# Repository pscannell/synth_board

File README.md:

# Synth Board

KiCad source files for synth hardware.

## Requirements

Kicad v6 ([download](kicad-unified-6.0.11-0.dmg))

## Getting Started

Open `synth.kicad_pro` from KiCad -> Open Project

Ensure that sch & pcb files can be opened

## Schematics

[See PDFs here](./docs/schematics/synth.pdf)

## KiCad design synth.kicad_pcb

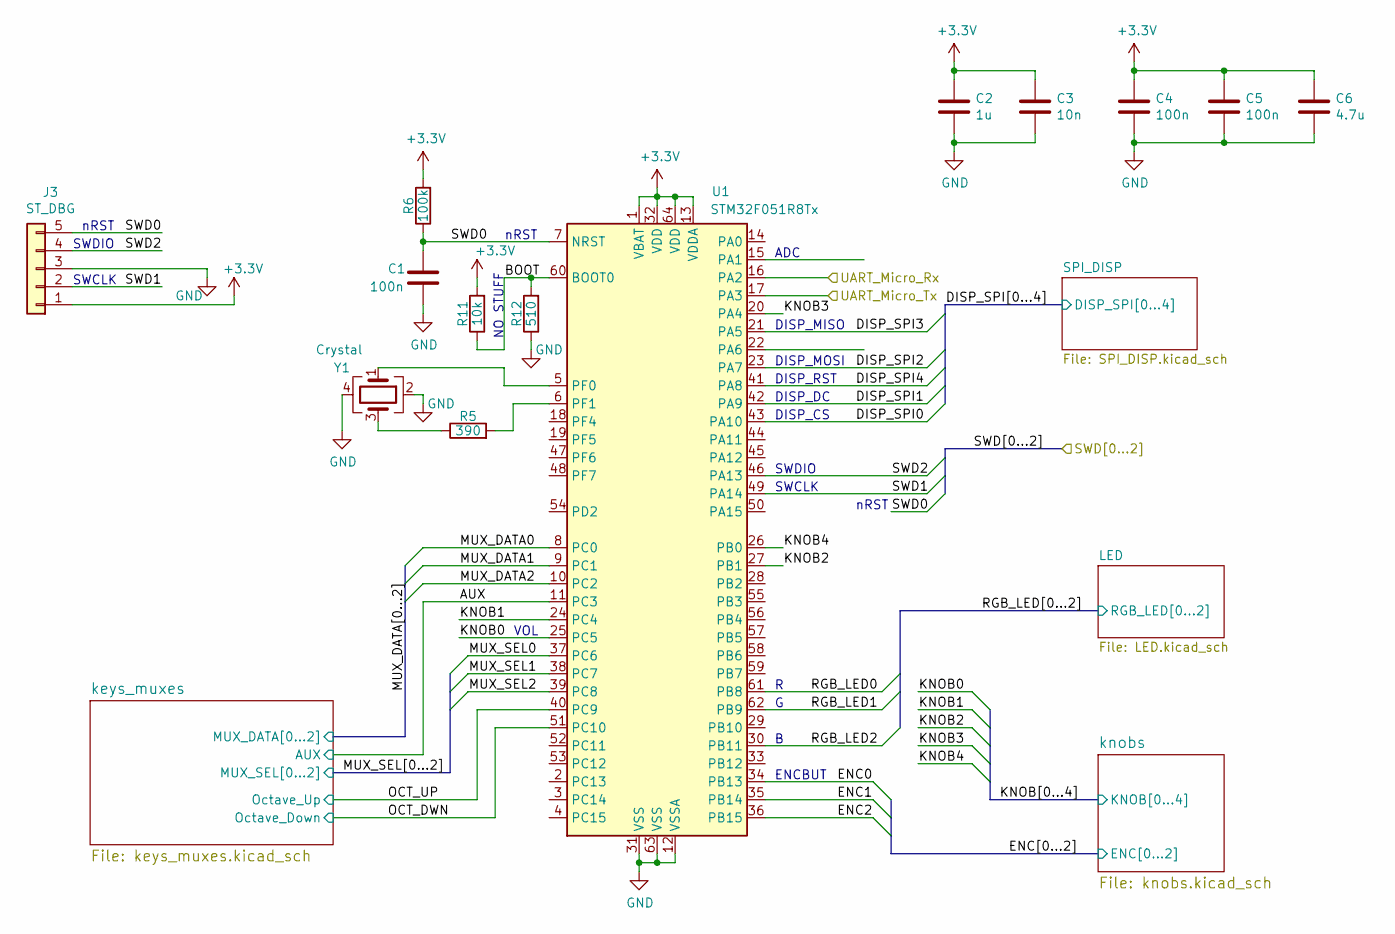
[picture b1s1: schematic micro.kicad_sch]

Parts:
C1, C4, C5: 100n; C_0603_HandSoldering
C2: 1u; C_0603_HandSoldering
C3: 10n; C_0603_HandSoldering
C6: 4.7u; C_0603_HandSoldering
J3: ST_DBG; Pin_Header_Straight_1x05_Pitch2.54mm
R5: 390; R_0603_HandSoldering
R6: 100k; R_0603_HandSoldering
R11: 10k; R_0603_HandSoldering
R12: 510; R_0603_HandSoldering
U1: STM32F051R8Tx; LQFP-64_10x10mm_Pitch0.5mm
Y1: Crystal; Crystal_SMD_Abracon_ABM3B-4pin_5.0x3.2mm

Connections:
/Raspberry_Pi_3/SWD0: C1.1, J3.5, R6.1, U1.7 (NRST); also elsewhere on the board
/Raspberry_Pi_3/SWD1: J3.2, U1.49 (PA14); also elsewhere on the board
/Raspberry_Pi_3/SWD2: J3.4, U1.46 (PA13); also elsewhere on the board
/micro/AUX: U1.11 (PC3); also elsewhere on the board
/micro/BOOT: R11.1, R12.2, U1.60 (BOOT0)
/micro/DISP_SPI0: U1.43 (PA10); also elsewhere on the board
/micro/DISP_SPI1: U1.42 (PA9); also elsewhere on the board
/micro/DISP_SPI2: U1.23 (PA7); also elsewhere on the board
/micro/DISP_SPI3: U1.21 (PA5); also elsewhere on the board
/micro/DISP_SPI4: U1.41 (PA8); also elsewhere on the board
/micro/ENC0: U1.34 (PB13); also elsewhere on the board
/micro/ENC1: U1.35 (PB14); also elsewhere on the board
/micro/ENC2: U1.36 (PB15); also elsewhere on the board
/micro/KNOB0: U1.25 (PC5); also elsewhere on the board
/micro/KNOB1: U1.24 (PC4); also elsewhere on the board
/micro/KNOB2: U1.27 (PB1); also elsewhere on the board
/micro/KNOB3: U1.20 (PA4); also elsewhere on the board
/micro/KNOB4: U1.26 (PB0); also elsewhere on the board
/micro/MUX_DATA0: U1.8 (PC0); also elsewhere on the board
/micro/MUX_DATA1: U1.9 (PC1); also elsewhere on the board
/micro/MUX_DATA2: U1.10 (PC2); also elsewhere on the board
/micro/MUX_SEL0: U1.37 (PC6); also elsewhere on the board
/micro/MUX_SEL1: U1.38 (PC7); also elsewhere on the board
/micro/MUX_SEL2: U1.39 (PC8); also elsewhere on the board
/micro/OCT_DWN: U1.51 (PC10); also elsewhere on the board
/micro/OCT_UP: U1.40 (PC9); also elsewhere on the board
/micro/RGB_LED0: U1.61 (PB8); also elsewhere on the board
/micro/RGB_LED1: U1.62 (PB9); also elsewhere on the board
/micro/RGB_LED2: U1.30 (PB11); also elsewhere on the board
/micro/UART_Micro_Rx: U1.16 (PA2); also elsewhere on the board
/micro/UART_Micro_Tx: U1.17 (PA3); also elsewhere on the board
GND: C1.2, C2.2, C3.2, C4.2, C5.2, C6.2, J3.3, R12.1, U1.12 (VSSA), U1.31 (VSS), U1.63 (VSS), Y1.2, Y1.4; also elsewhere on the board
unnamed: R5.1, Y1.3
unnamed: R5.2, U1.6 (PF1)
unnamed: U1.5 (PF0), Y1.1

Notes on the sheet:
DISP_MOSI
SWDIO
SWCLK
nRST
NO STUFF
DISP_CS
DISP_RST
ADC
DISP_DC
DISP_MISO
ENCBUT
VOL

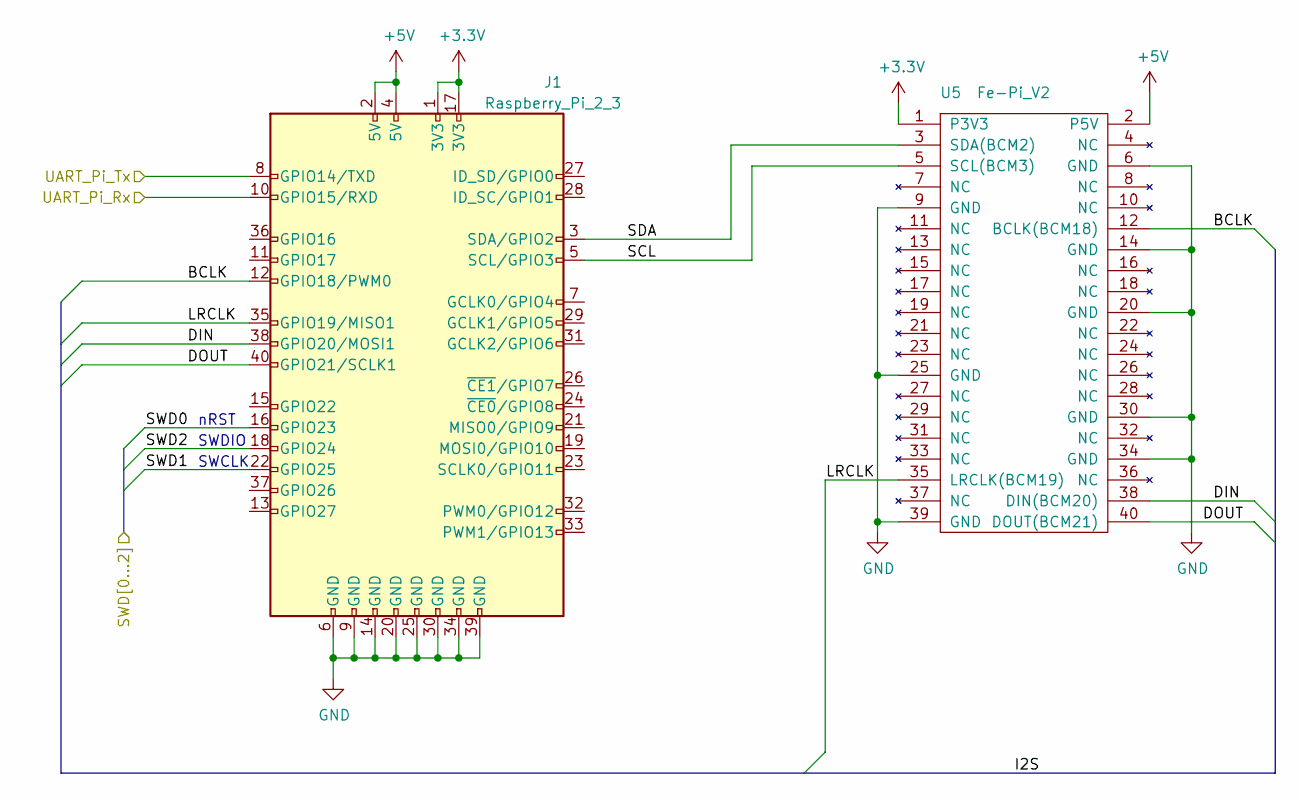
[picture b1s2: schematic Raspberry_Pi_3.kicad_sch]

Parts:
J1: Raspberry_Pi_2_3; RPi_A+
U5: Fe-Pi_V2; Fe_Pi_V2

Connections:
+5V: J1.2 (5V), J1.4 (5V), U5.2 (P5V); also elsewhere on the board
/Raspberry_Pi_3/BCLK: J1.12 (GPIO18/PWM0), U5.12 (BCLK(BCM18))
/Raspberry_Pi_3/DIN: J1.38 (GPIO20/MOSI1), U5.38 (DIN(BCM20))
/Raspberry_Pi_3/DOUT: J1.40 (GPIO21/SCLK1), U5.40 (DOUT(BCM21))
/Raspberry_Pi_3/LRCLK: J1.35 (GPIO19/MISO1), U5.35 (LRCLK(BCM19))
/Raspberry_Pi_3/SCL: J1.5 (SCL/GPIO3), U5.5 (SCL(BCM3))
/Raspberry_Pi_3/SDA: J1.3 (SDA/GPIO2), U5.3 (SDA(BCM2))
/Raspberry_Pi_3/SWD0: J1.16 (GPIO23); also elsewhere on the board
/Raspberry_Pi_3/SWD1: J1.22 (GPIO25); also elsewhere on the board
/Raspberry_Pi_3/SWD2: J1.18 (GPIO24); also elsewhere on the board
/micro/UART_Micro_Rx: J1.8 (GPIO14/TXD); also elsewhere on the board
/micro/UART_Micro_Tx: J1.10 (GPIO15/RXD); also elsewhere on the board
GND: J1.6 (GND), J1.9 (GND), J1.14 (GND), J1.20 (GND), J1.25 (GND), J1.30 (GND), J1.34 (GND), J1.39 (GND), U5.6 (GND), U5.9 (GND), U5.14 (GND), U5.20 (GND), U5.25 (GND), U5.30 (GND), U5.34 (GND), U5.39 (GND); also elsewhere on the board

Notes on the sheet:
SWCLK
SWDIO
nRST

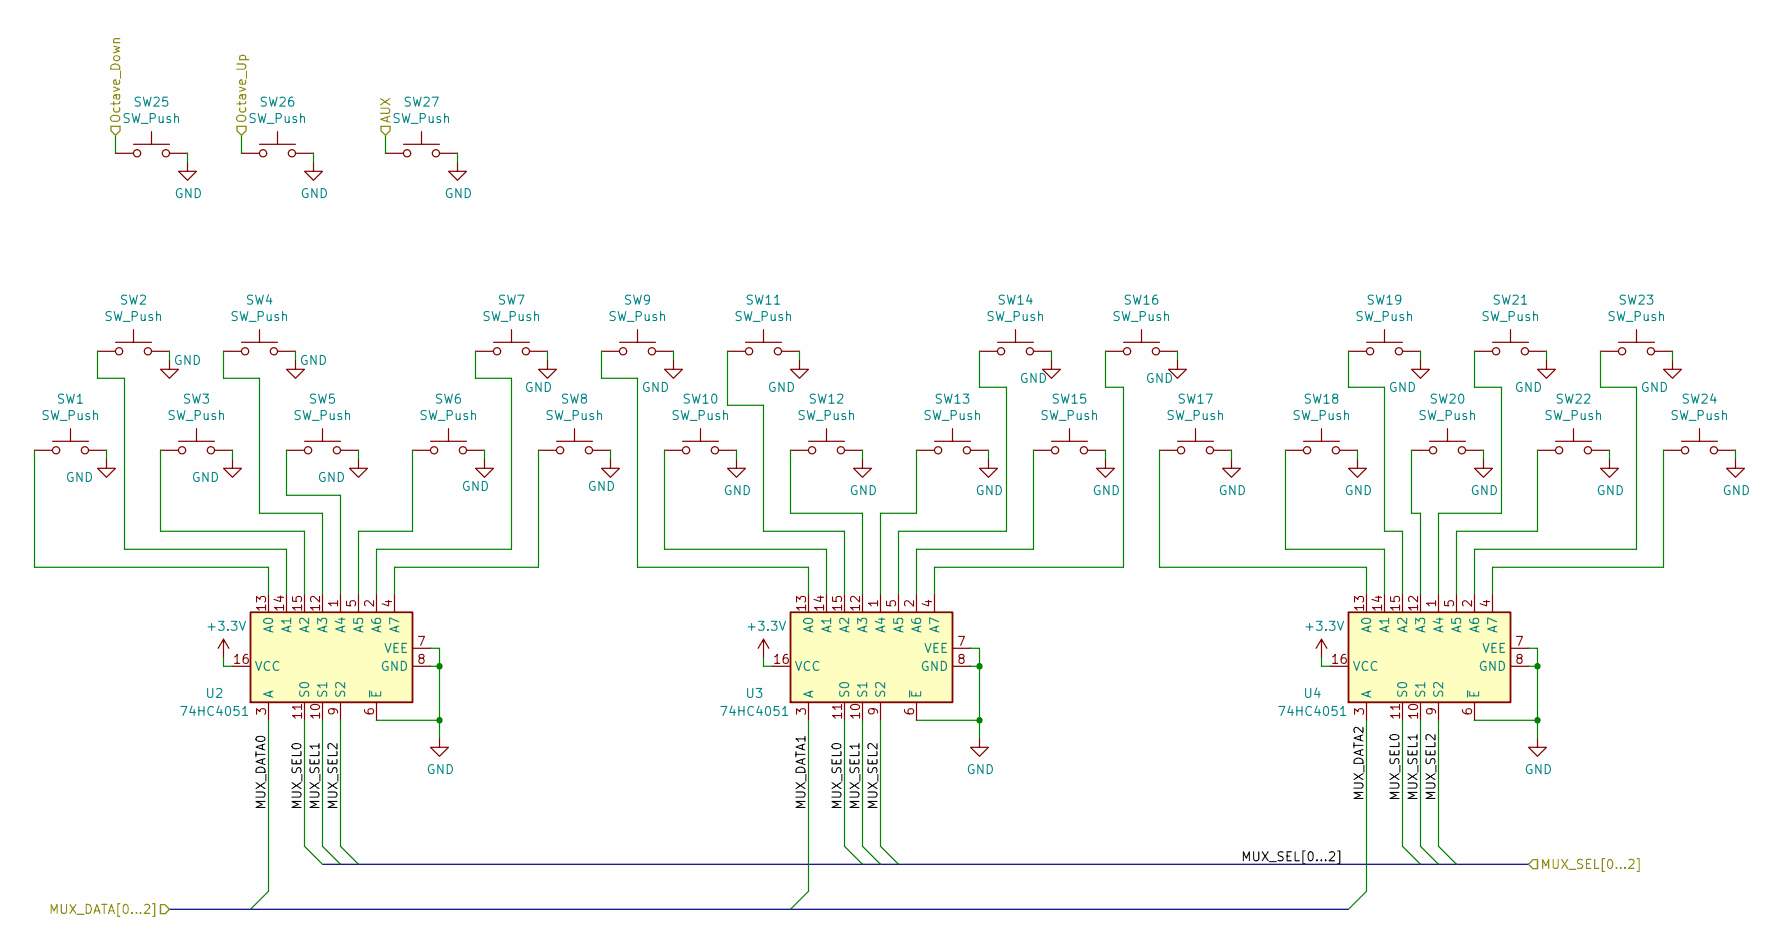
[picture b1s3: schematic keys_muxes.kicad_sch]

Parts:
SW1, SW2, SW3, SW4, SW5, SW6, SW7, SW8, SW9, SW10, SW11, SW12, SW13, SW14, SW15, SW16, SW17, SW18, SW19, SW20, SW21, SW22, SW23, SW24, SW25, SW26, SW27: SW_Push; SW_SPST_PTS645
U2, U3, U4: 74HC4051; SOIC-16W_5.3x10.2mm_Pitch1.27mm

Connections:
/micro/AUX: SW27.1; also elsewhere on the board
/micro/MUX_DATA0: U2.3 (A); also elsewhere on the board
/micro/MUX_DATA1: U3.3 (A); also elsewhere on the board
/micro/MUX_DATA2: U4.3 (A); also elsewhere on the board
/micro/MUX_SEL0: U2.11 (S0), U3.11 (S0), U4.11 (S0); also elsewhere on the board
/micro/MUX_SEL1: U2.10 (S1), U3.10 (S1), U4.10 (S1); also elsewhere on the board
/micro/MUX_SEL2: U2.9 (S2), U3.9 (S2), U4.9 (S2); also elsewhere on the board
/micro/OCT_DWN: SW25.1; also elsewhere on the board
/micro/OCT_UP: SW26.1; also elsewhere on the board
GND: SW1.2, SW2.2, SW3.2, SW4.2, SW5.2, SW6.2, SW7.2, SW8.2, SW9.2, SW10.2, SW11.2, SW12.2, SW13.2, SW14.2, SW15.2, SW16.2, SW17.2, SW18.2, SW19.2, SW20.2, SW21.2, SW22.2, SW23.2, SW24.2, SW25.2, SW26.2, SW27.2, U2.6 (~E), U2.7 (VEE), U2.8 (GND), U3.6 (~E), U3.7 (VEE), U3.8 (GND), U4.6 (~E), U4.7 (VEE), U4.8 (GND); also elsewhere on the board
unnamed: SW1.1, U2.13 (A0)
unnamed: SW2.1, U2.14 (A1)
unnamed: SW3.1, U2.15 (A2)
unnamed: SW4.1, U2.12 (A3)
unnamed: SW5.1, U2.1 (A4)
unnamed: SW6.1, U2.5 (A5)
unnamed: SW7.1, U2.2 (A6)
unnamed: SW8.1, U2.4 (A7)
unnamed: SW9.1, U3.13 (A0)
unnamed: SW10.1, U3.14 (A1)
unnamed: SW11.1, U3.15 (A2)
unnamed: SW12.1, U3.12 (A3)
unnamed: SW13.1, U3.1 (A4)
unnamed: SW14.1, U3.5 (A5)
unnamed: SW15.1, U3.2 (A6)
unnamed: SW16.1, U3.4 (A7)
unnamed: SW17.1, U4.13 (A0)
unnamed: SW18.1, U4.14 (A1)
unnamed: SW19.1, U4.15 (A2)
unnamed: SW20.1, U4.12 (A3)
unnamed: SW21.1, U4.1 (A4)
unnamed: SW22.1, U4.5 (A5)
unnamed: SW23.1, U4.2 (A6)
unnamed: SW24.1, U4.4 (A7)

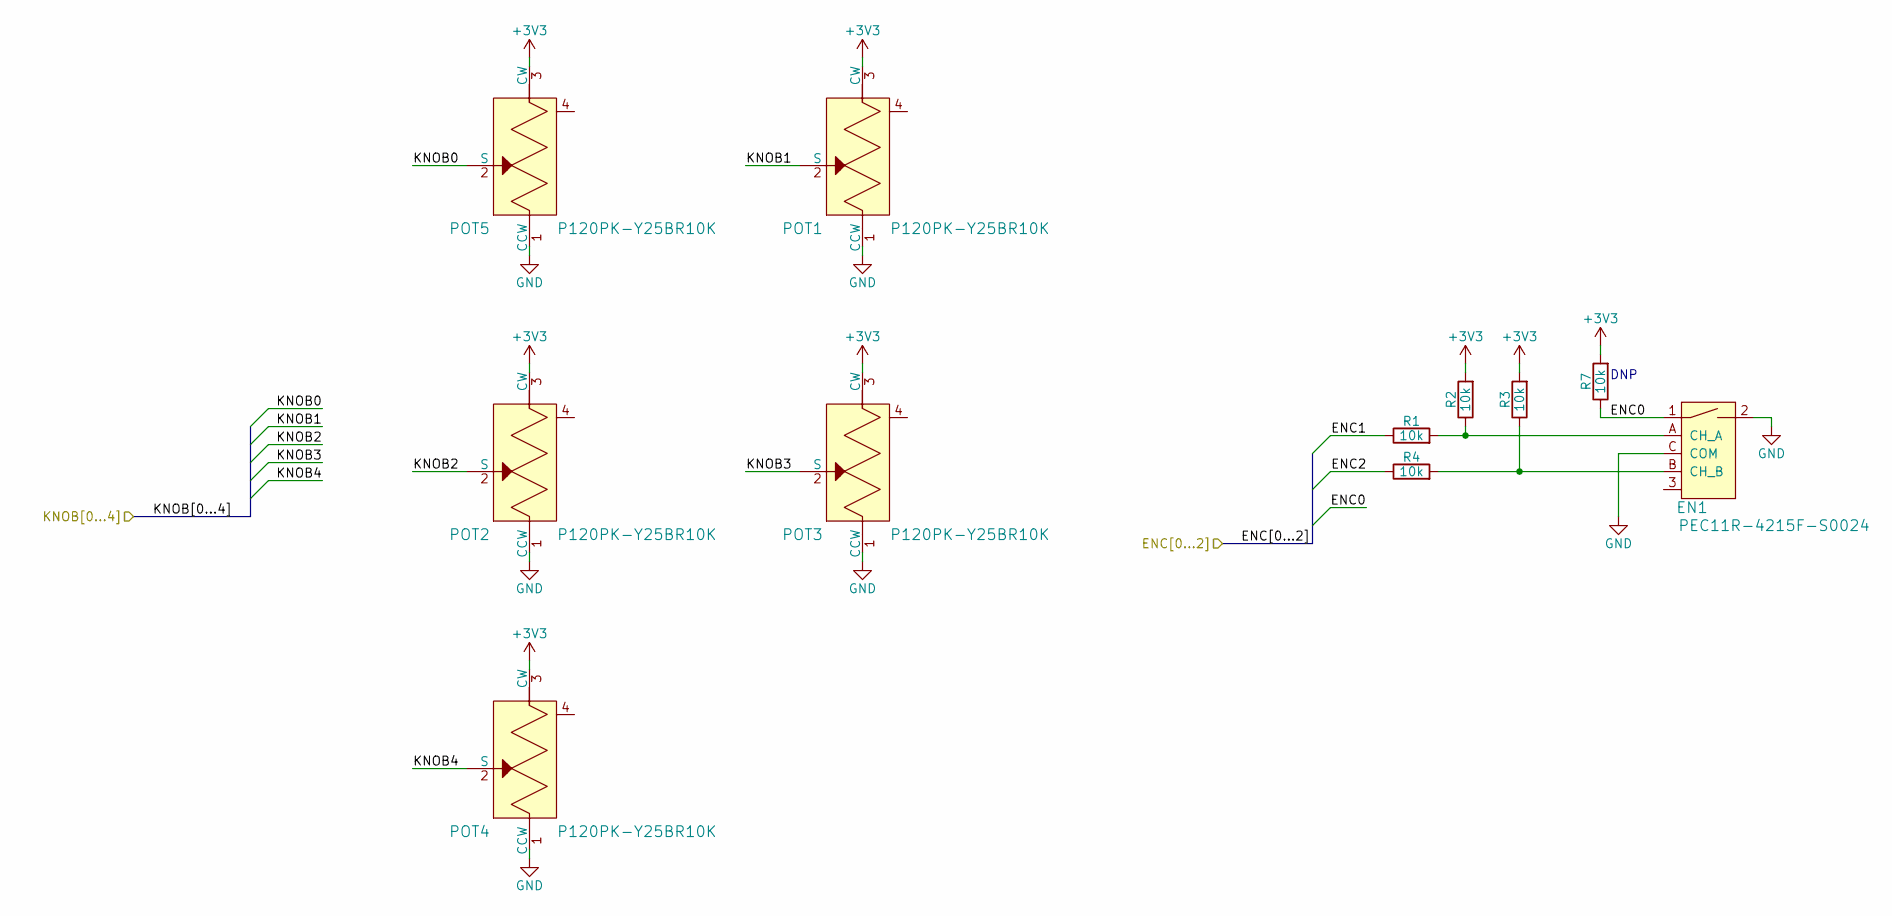
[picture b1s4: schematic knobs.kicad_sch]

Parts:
EN1: PEC11R-4215F-S0024; Rotary_Encoder_Switched_PEC11R; MPN PEC11R-4215F-S0024; Digi-Key_PN PEC11R-4215F-S0024-ND
POT1, POT2, POT3, POT4, POT5: P120PK-Y25BR10K; Potentiometer_P120PK-Y25BR10K; MPN P120PK-Y25BR10K; Digi-Key_PN 987-1710-ND
R1, R2, R3, R4, R7: 10k; R_0603_HandSoldering

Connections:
/micro/ENC0: EN1.1, R7.1; also elsewhere on the board
/micro/ENC1: R1.1; also elsewhere on the board
/micro/ENC2: R4.1; also elsewhere on the board
/micro/KNOB0: POT5.2 (S); also elsewhere on the board
/micro/KNOB1: POT1.2 (S); also elsewhere on the board
/micro/KNOB2: POT2.2 (S); also elsewhere on the board
/micro/KNOB3: POT3.2 (S); also elsewhere on the board
/micro/KNOB4: POT4.2 (S); also elsewhere on the board
GND: EN1.2, EN1.C (COM), POT1.1 (CCW), POT2.1 (CCW), POT3.1 (CCW), POT4.1 (CCW), POT5.1 (CCW); also elsewhere on the board
unnamed: EN1.A (CH_A), R1.2, R2.1
unnamed: EN1.B (CH_B), R3.1, R4.2

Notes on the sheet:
DNP

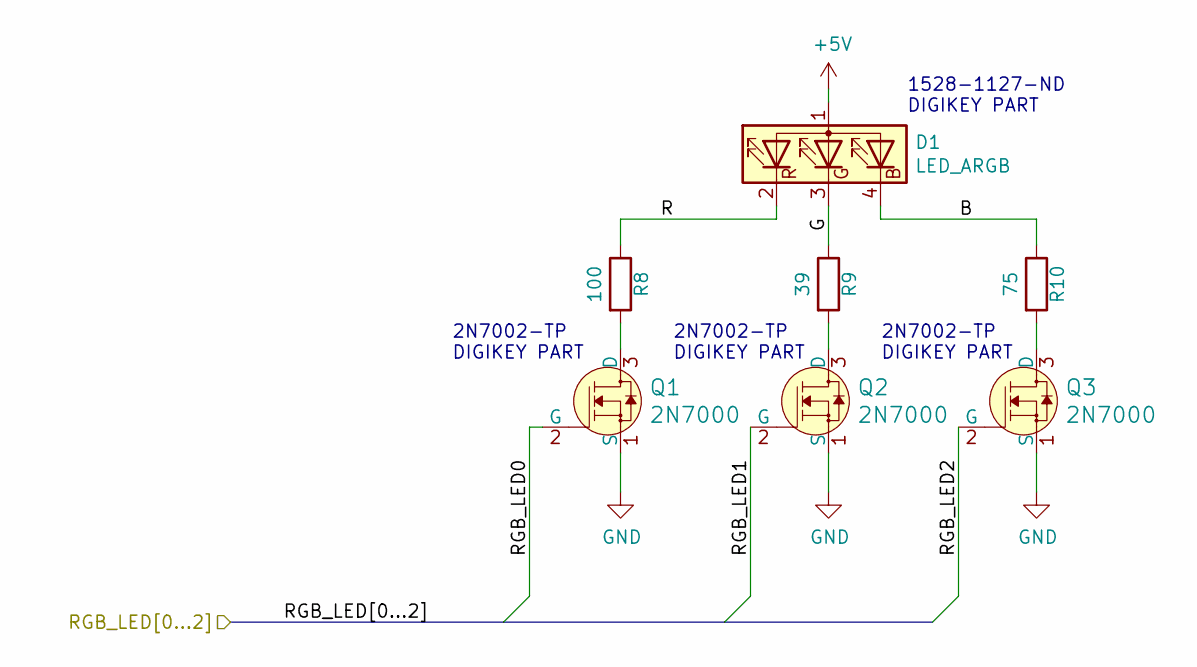
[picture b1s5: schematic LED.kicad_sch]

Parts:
D1: LED_ARGB; Piranha_Super_flux_RGB
Q1, Q2, Q3: 2N7000; SOT-23_Handsoldering; MPN 2N7000; Digi-Key_PN 2N7000FS-ND
R8: 100; R_0603_HandSoldering
R9: 39; R_0603_HandSoldering
R10: 75; R_0603_HandSoldering

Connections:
+5V: D1.1 (A); also elsewhere on the board
/micro/LED/B: D1.4 (BK), R10.1
/micro/LED/G: D1.3 (GK), R9.1
/micro/LED/R: D1.2 (RK), R8.1
/micro/RGB_LED0: Q1.2 (G); also elsewhere on the board
/micro/RGB_LED1: Q2.2 (G); also elsewhere on the board
/micro/RGB_LED2: Q3.2 (G); also elsewhere on the board
GND: Q1.1 (S), Q2.1 (S), Q3.1 (S); also elsewhere on the board
unnamed: Q1.3 (D), R8.2
unnamed: Q2.3 (D), R9.2
unnamed: Q3.3 (D), R10.2

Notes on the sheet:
2N7002-TP DIGIKEY PART
1528-1127-ND DIGIKEY PART

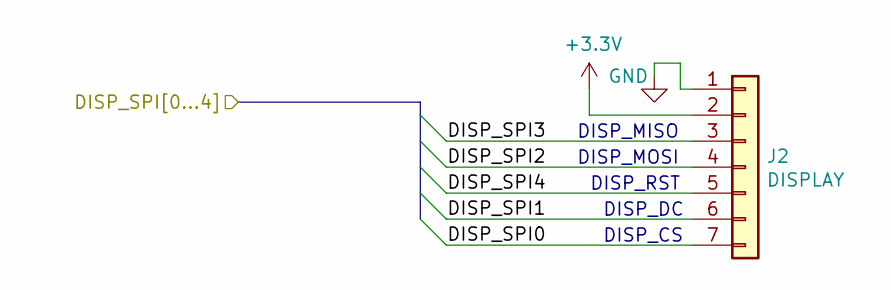
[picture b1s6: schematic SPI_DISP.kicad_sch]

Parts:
J2: DISPLAY; SSD_1306

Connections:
/micro/DISP_SPI0: J2.7; also elsewhere on the board
/micro/DISP_SPI1: J2.6; also elsewhere on the board
/micro/DISP_SPI2: J2.4; also elsewhere on the board
/micro/DISP_SPI3: J2.3; also elsewhere on the board
/micro/DISP_SPI4: J2.5; also elsewhere on the board
GND: J2.1; also elsewhere on the board

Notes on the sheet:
DISP_MOSI
DISP_RST
DISP_DC
DISP_MISO
DISP_CS

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
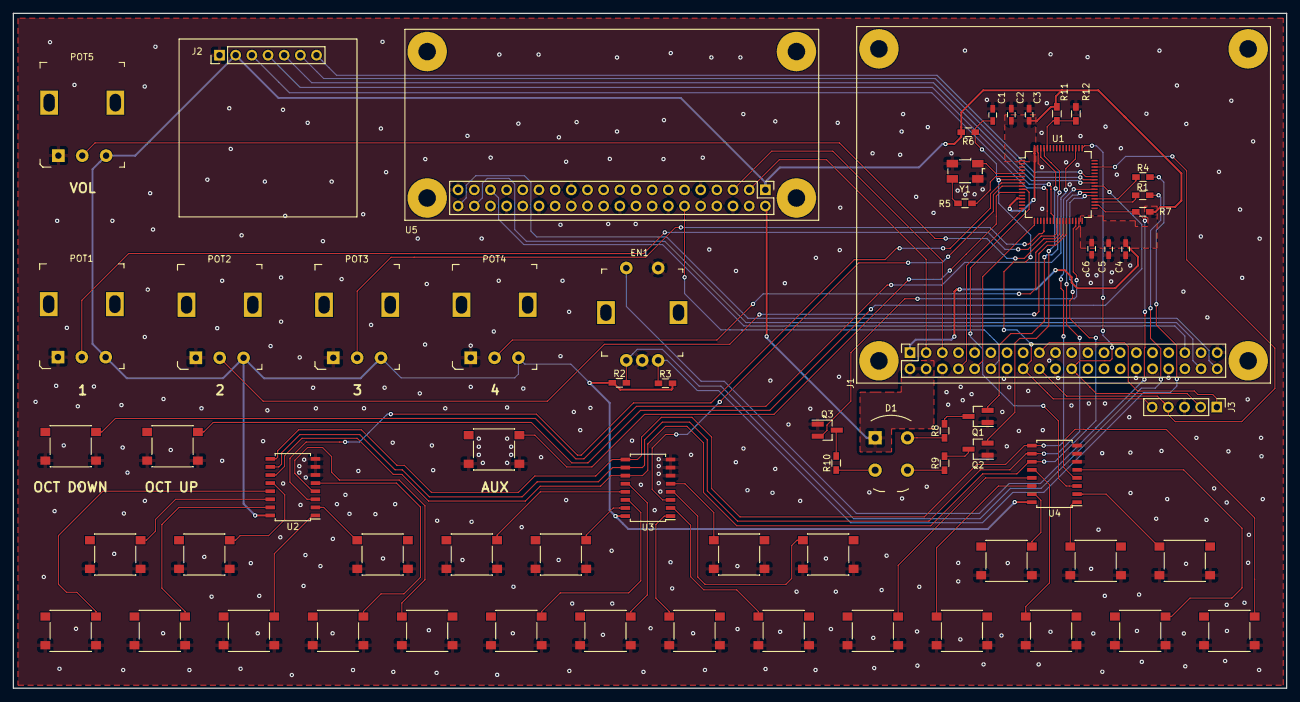
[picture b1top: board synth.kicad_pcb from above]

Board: 2 copper layers, 200.0 x 106.0 mm, 64 parts (0 on the bottom side), 75 nets.

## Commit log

2023-10-11 Initial commit - Adding board files + README
2026-01-13 update to Kicad v9
